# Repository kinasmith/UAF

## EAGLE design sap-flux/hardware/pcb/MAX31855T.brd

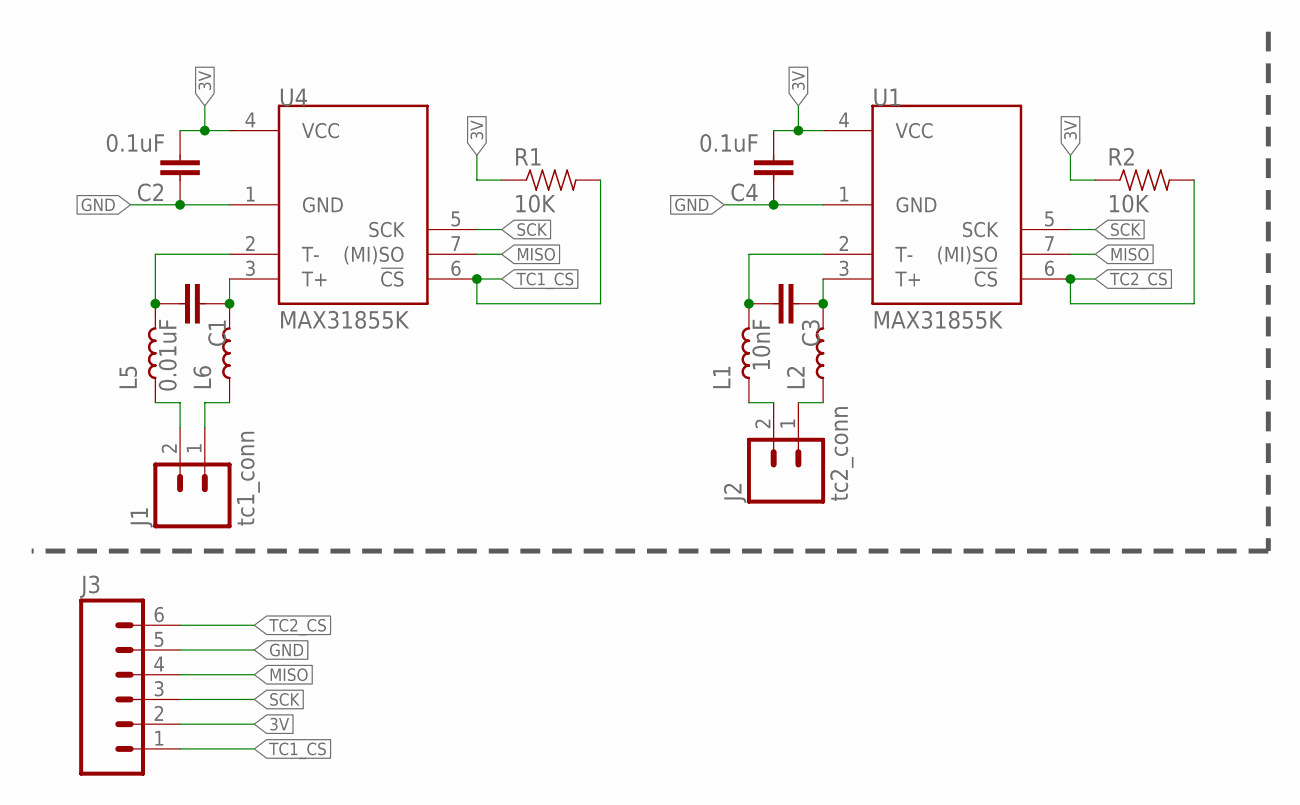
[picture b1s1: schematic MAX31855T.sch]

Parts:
C1: 0.01uF; 0603-CAP
C2, C4: 0.1uF; 0603-CAP
C3: 10nF; 0603-CAP
J1: tc1_conn; 1X02_LONGPADS
J2: tc2_conn; 1X02_LONGPADS
J3: M06LONGPADS; 1X06_LONGPADS
L1, L2, L5, L6: INDUCTOR0603-N; L0603-N
R1, R2: 10K; 0603-RES
U1, U4: MAX31855K; SOIC8

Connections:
3V: C2.2, C4.2, J3.2, R1.1, R2.1, U1.4 (VCC), U4.4 (VCC)
GND: C2.1, C4.1, J3.5, U1.1 (GND), U4.1 (GND)
MISO: J3.4, U1.7 ((MI)SO), U4.7 ((MI)SO)
unnamed: C3.2, L1.2, U1.2 (T-)
unnamed: C3.1, L2.2, U1.3 (T+)
unnamed: J1.1, L6.1
unnamed: J1.2, L5.1
unnamed: J2.1, L2.1
unnamed: C1.2, L5.2, U4.2 (T-)
unnamed: C1.1, L6.2, U4.3 (T+)
unnamed: J2.2, L1.1
SCK: J3.3, U1.5 (SCK), U4.5 (SCK)
TC1_CS: J3.1, R1.2, U4.6 (!CS)
TC2_CS: J3.6, R2.2, U1.6 (!CS)

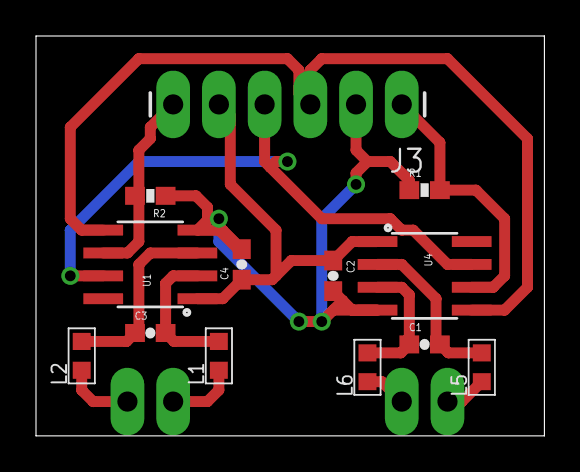
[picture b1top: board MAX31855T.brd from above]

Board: 2 copper layers, 28.2 x 22.2 mm, 15 parts (0 on the bottom side), 14 nets.

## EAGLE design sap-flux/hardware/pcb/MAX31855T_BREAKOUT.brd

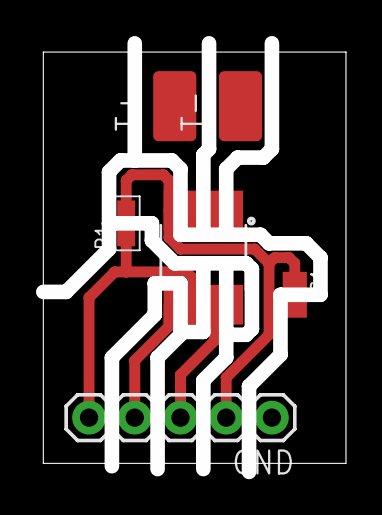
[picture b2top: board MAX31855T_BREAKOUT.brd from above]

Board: 2 copper layers, 16.8 x 22.9 mm, 6 parts (0 on the bottom side), 7 nets.

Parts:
C1: 0.1µF; C0805-L
GND: 1X05
R1: 10k; R0603-N
T+: LUXEON-PAD
T-: LUXEON-PAD
U1: MAX31855K; SOIC8

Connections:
CS: GND.5, R1.1, U1.6
MISO: GND.3, U1.7
unnamed: C1.2, GND.1, U1.1
unnamed: T-.P$1, U1.2
unnamed: T+.P$1, U1.3
unnamed: C1.1, GND.2, R1.2, U1.4
SCK: GND.4, U1.5

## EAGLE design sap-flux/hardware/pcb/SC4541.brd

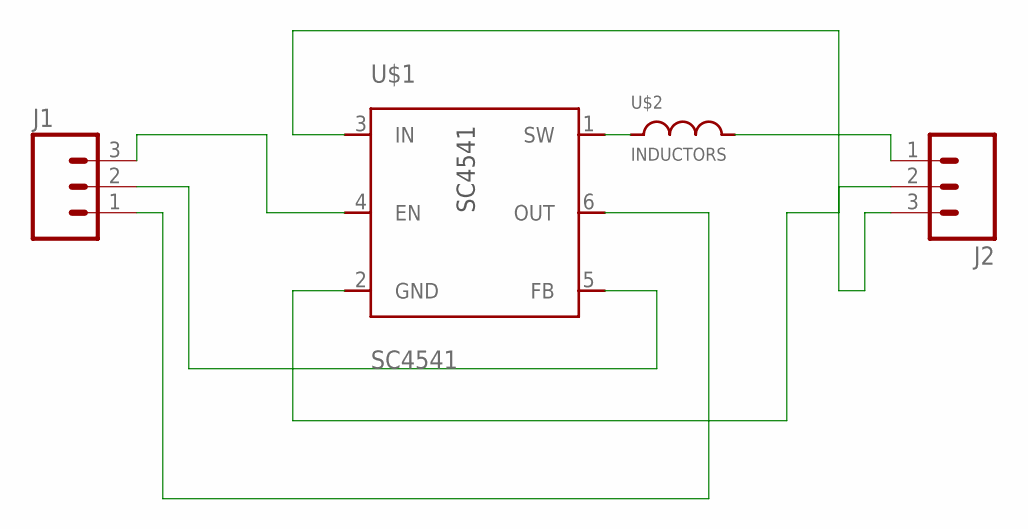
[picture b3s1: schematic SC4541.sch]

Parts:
J1, J2: M03PTH; 1X03
U$1: SC4541; SOT23-6
U$2: INDUCTORS; 1212_3X3

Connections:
unnamed: J1.3, U$1.4 (EN)
unnamed: J1.2, U$1.5 (FB)
unnamed: U$1.1 (SW), U$2.P$2
unnamed: J1.1, U$1.6 (OUT)
unnamed: J2.2, U$1.2 (GND)
unnamed: J2.3, U$1.3 (IN)
unnamed: J2.1, U$2.P$1

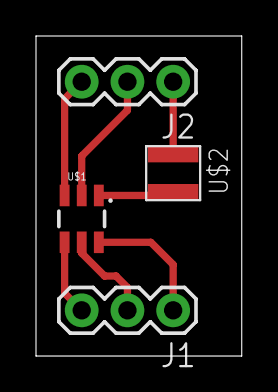
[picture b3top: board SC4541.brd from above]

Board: 2 copper layers, 11.4 x 17.8 mm, 4 parts (0 on the bottom side), 7 nets.

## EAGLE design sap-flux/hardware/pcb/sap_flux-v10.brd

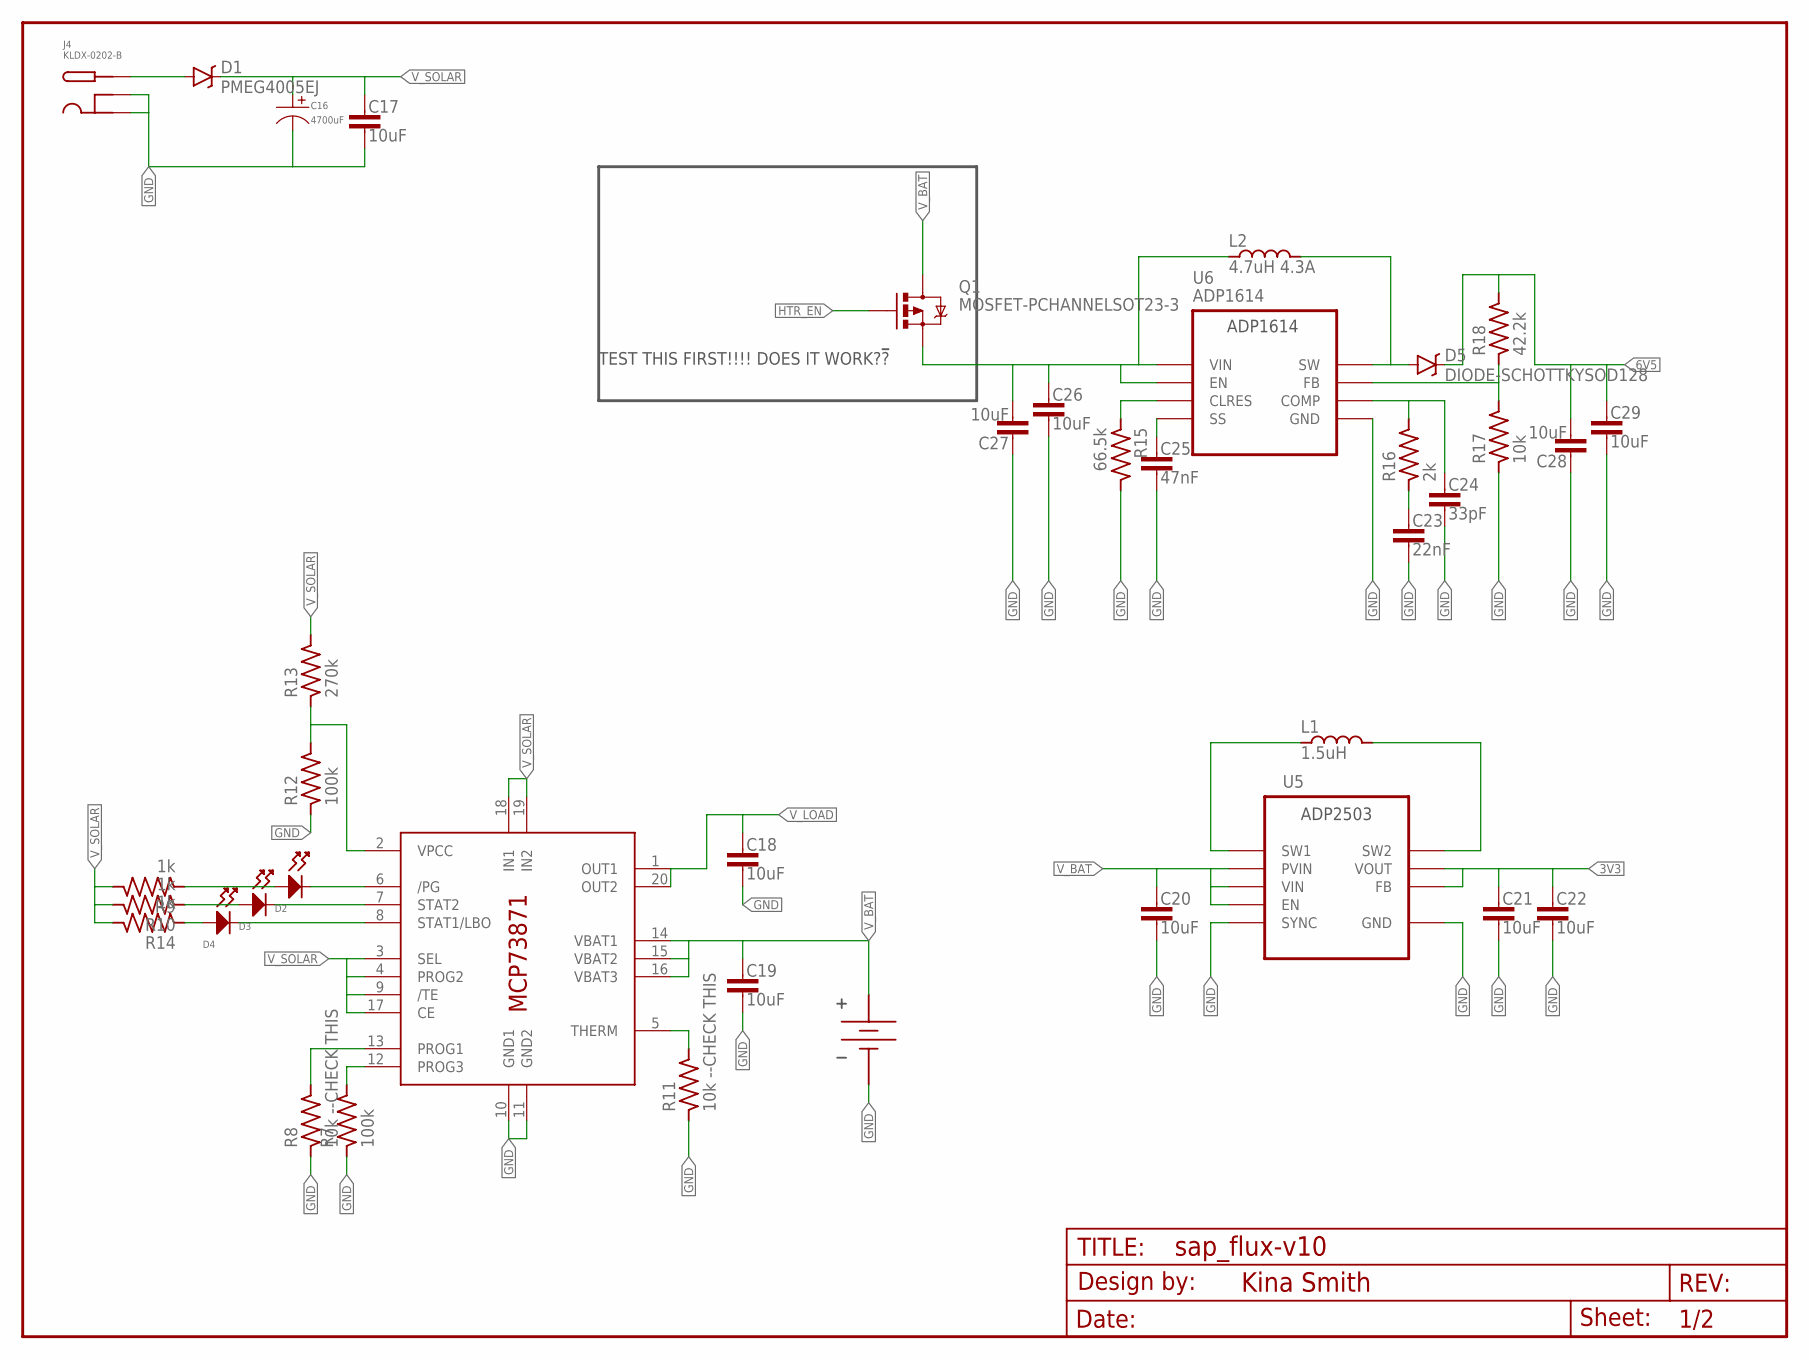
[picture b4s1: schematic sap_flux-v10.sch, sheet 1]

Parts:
BATT1: BATTERY_HOLDER18650; BAT_18650-KEYSTONE-1043
C16: 4700uF; CP10MM
C17, C18, C19, C20, C21, C22, C26, C27, C28, C29: 10uF; C0805-N
C23: 22nF; C0603-N
C24: 33pF; C0603-N
C25: 47nF; C0603-N
D1: PMEG4005EJ; SOD-323
D2, D3, D4: LED_SINGLE-0603; LED0603
D5: DIODE-SCHOTTKYSOD128; SOD128
FRAME1: FRAME-LETTER; CREATIVE_COMMONS
J4: KLDX-0202-B; DC_PWR_JACK; PARTNO FIND THIS PART AND CHECK FOOTPRINT
L1: 1.5uH; L3030
L2: 4.7uH 4.3A; L8080
Q1: MOSFET-PCHANNELSOT23-3; SOT23-3
R7, R12: 100k; R0603-N
R8, R11: 10k --CHECK THIS; R0603-N
R9, R10, R14: 1k; R0603-N
R13: 270k; R0603-N
R15: 66.5k; R0603-N
R16: 2k; R0603-N
R17: 10k; R0603-N
R18: 42.2k; R0603-N
U4: MCP73871; QFN20
U5: ADP2503; DFN300X300X80-11N
U6: ADP1614; DFN300X300X80-11N

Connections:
3V3: C21.1, C22.1, U5.1 (VOUT), U5.10 (FB); also elsewhere on the board
6V5: C28.2, C29.1, D5.C-1 (C), R18.2
6V5_VIN: C26.1, C27.2, L2.1, Q1.2 (S), U6.3 (EN), U6.8 (VIN)
GND: BATT1.NEG (GND), C16.P$2, C17.2, C18.2, C19.2, C20.2, C21.2, C22.2, C23.2, C24.2, C25.2, C26.2, C27.1, C28.1, C29.2, J4.SLEEVE1 (SLEEVE), J4.SLEEVE2 (SLEEVE_SHUNT), R7.1, R8.1, R11.1, R12.1, R15.2, R17.1, U4.10 (GND1), U4.11 (GND2), U5.3 (GND), U5.7 (SYNC), U5.9 (GND), U5.11 (GND), U6.4 (GND), U6.5 (GND), U6.11 (GND); also elsewhere on the board
HTR_EN: Q1.1 (G)
unnamed: D1.A, J4.PIN
unnamed: D2.CATHODE, U4.6 (/PG)
unnamed: R12.2, R13.1, U4.2 (VPCC)
unnamed: D3.CATHODE, U4.7 (STAT2)
unnamed: D4.CATHODE, U4.8 (STAT1/LBO)
unnamed: R8.2, U4.13 (PROG1)
unnamed: R7.2, U4.12 (PROG3)
unnamed: D2.ANODE, R9.1
unnamed: D3.ANODE, R10.1
unnamed: D4.ANODE, R14.1
unnamed: L1.P$1, U5.4 (SW1)
unnamed: L1.P$2, U5.2 (SW2)
unnamed: C25.1, U6.10 (SS)
unnamed: R15.1, U6.9 (CLRES)
unnamed: D5.A-2 (A), L2.2, U6.6 (SW), U6.7 (SW)
unnamed: R17.2, R18.1, U6.2 (FB)
unnamed: C24.1, R16.2, U6.1 (COMP)
unnamed: C23.1, R16.1
V_BAT: BATT1.POS (VBAT), C19.1, C20.1, Q1.3 (D), U4.14 (VBAT1), U4.15 (VBAT2), U4.16 (VBAT3), U5.5 (PVIN), U5.6 (EN), U5.8 (VIN)
V_LOAD: C18.1, U4.1 (OUT1), U4.20 (OUT2)
V_SOLAR: C16.P$1, C17.1, D1.C, R9.2, R10.2, R13.2, R14.2, U4.3 (SEL), U4.4 (PROG2), U4.9 (/TE), U4.17 (CE), U4.18 (IN1), U4.19 (IN2)

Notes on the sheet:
TEST THIS FIRST!!!! DOES IT WORK?!?!

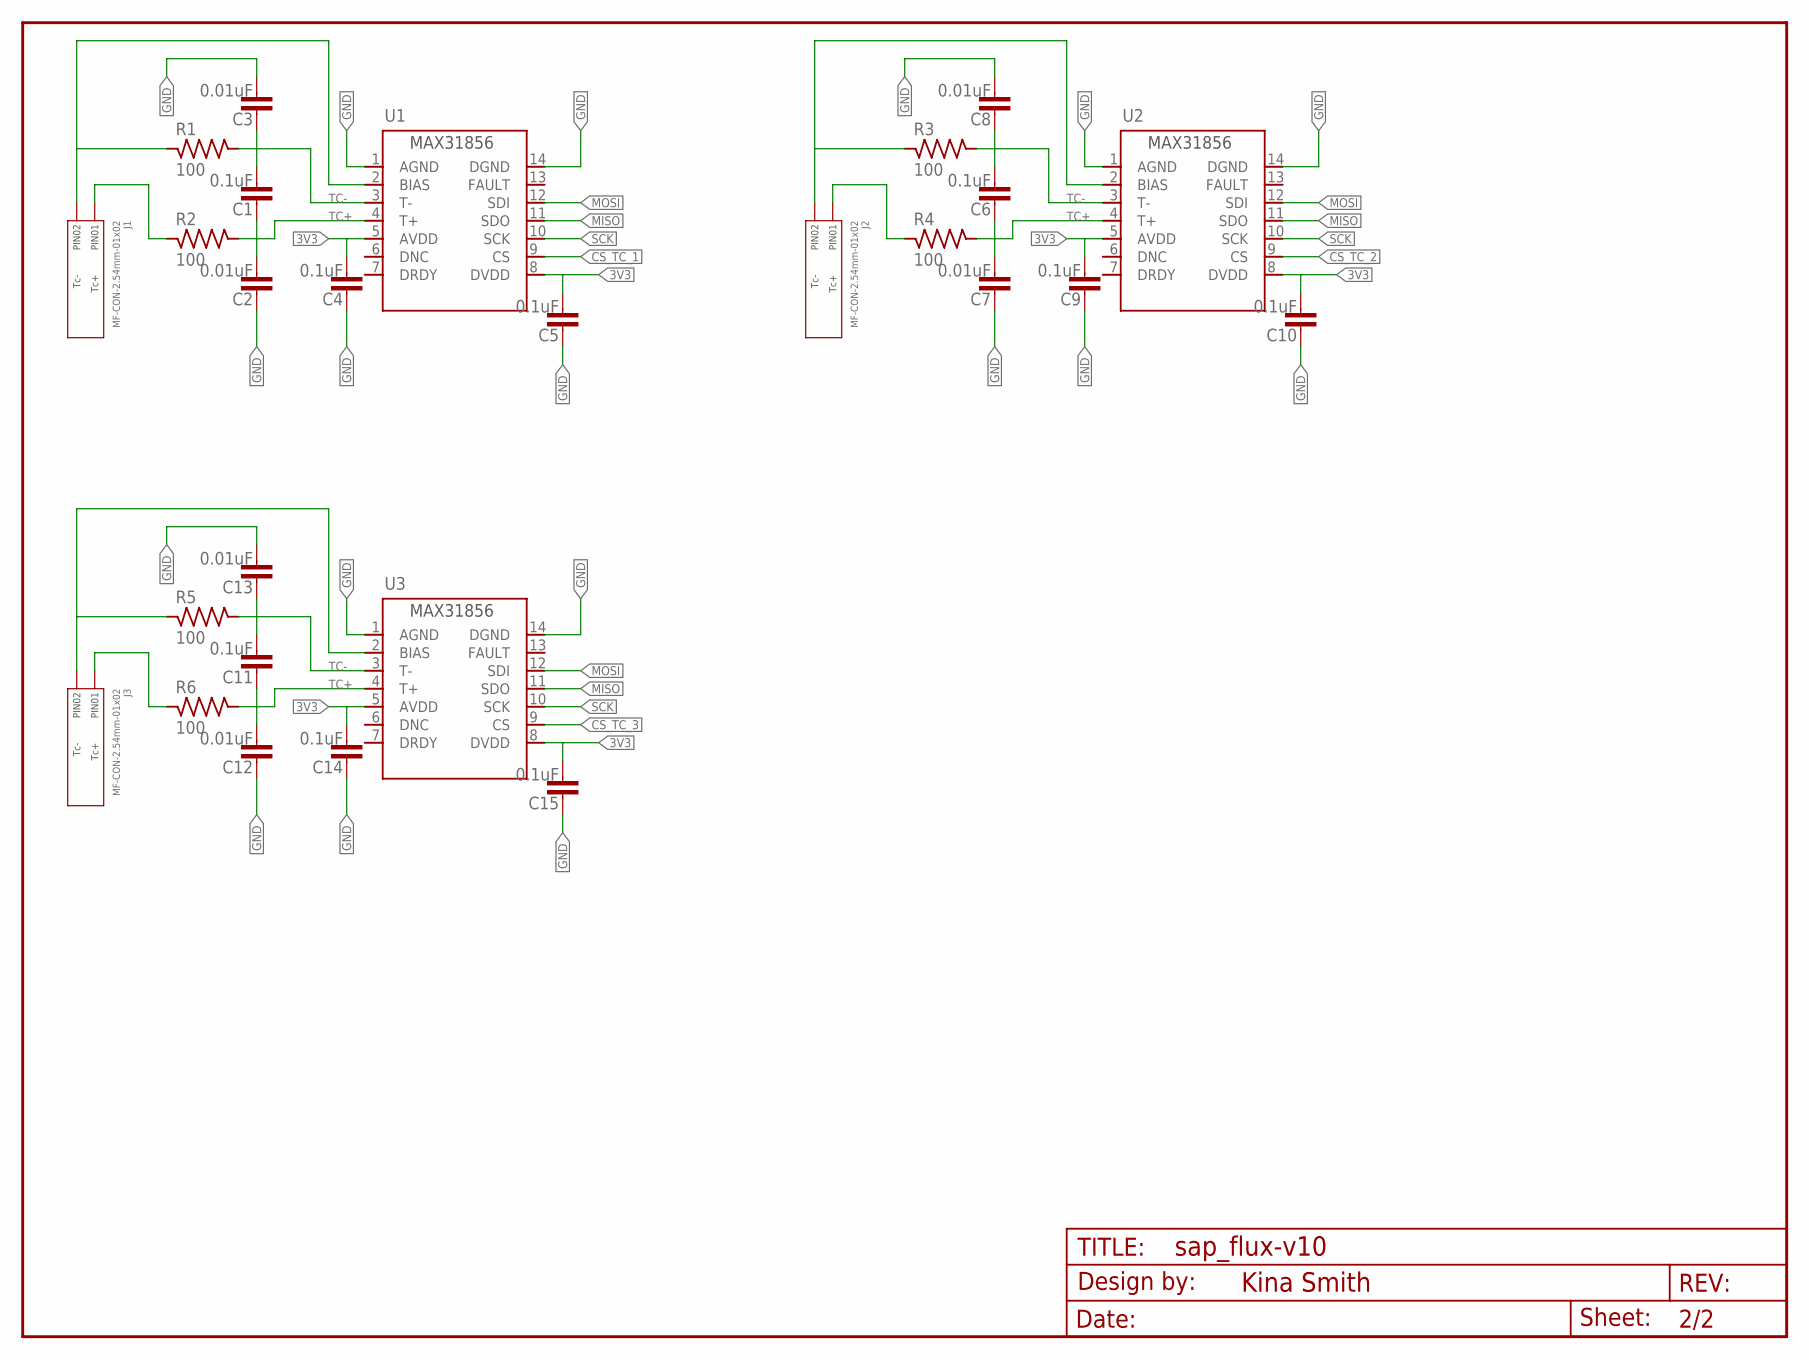
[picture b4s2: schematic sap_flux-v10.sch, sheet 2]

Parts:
C1, C4, C5, C6, C9, C10, C11, C14, C15: 0.1uF; C0603-N
C2, C3, C7, C8, C12, C13: 0.01uF; C0603-N
FRAME2: FRAME-LETTERNO_PACKAGE; DUMMY
J1, J2, J3: MF-CON-2.54mm-01x02; PTH_2.54MM_01X02
R1, R2, R3, R4, R5, R6: 100; R0603-N
U1, U2, U3: MAX31856MUD+; TSSOP14

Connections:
3V3: C4.2, C5.2, C9.2, C10.2, C14.2, C15.2, U1.5 (AVDD), U1.8 (DVDD), U2.5 (AVDD), U2.8 (DVDD), U3.5 (AVDD), U3.8 (DVDD); also elsewhere on the board
CS_TC_1: U1.9 (CS)
CS_TC_2: U2.9 (CS)
CS_TC_3: U3.9 (CS)
GND: C2.1, C3.2, C4.1, C5.1, C7.1, C8.2, C9.1, C10.1, C12.1, C13.2, C14.1, C15.1, U1.1 (AGND), U1.14 (DGND), U2.1 (AGND), U2.14 (DGND), U3.1 (AGND), U3.14 (DGND); also elsewhere on the board
MISO: U1.11 (SDO), U2.11 (SDO), U3.11 (SDO)
MOSI: U1.12 (SDI), U2.12 (SDI), U3.12 (SDI)
unnamed: J2.P$1 (PIN1), R4.1
unnamed: J2.P$2 (PIN2), R3.1, U2.2 (BIAS)
unnamed: J3.P$1 (PIN1), R6.1
unnamed: J3.P$2 (PIN2), R5.1, U3.2 (BIAS)
unnamed: J1.P$1 (PIN1), R2.1
unnamed: J1.P$2 (PIN2), R1.1, U1.2 (BIAS)
SCK: U1.10 (SCK), U2.10 (SCK), U3.10 (SCK)
TC+: C1.1, C2.2, C6.1, C7.2, C11.1, C12.2, R2.2, R4.2, R6.2, U1.4 (T+), U2.4 (T+), U3.4 (T+)
TC-: C1.2, C3.1, C6.2, C8.1, C11.2, C13.1, R1.2, R3.2, R5.2, U1.3 (T-), U2.3 (T-), U3.3 (T-)

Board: 2 copper layers, 68 parts (0 on the bottom side), 36 nets, no tracks yet.

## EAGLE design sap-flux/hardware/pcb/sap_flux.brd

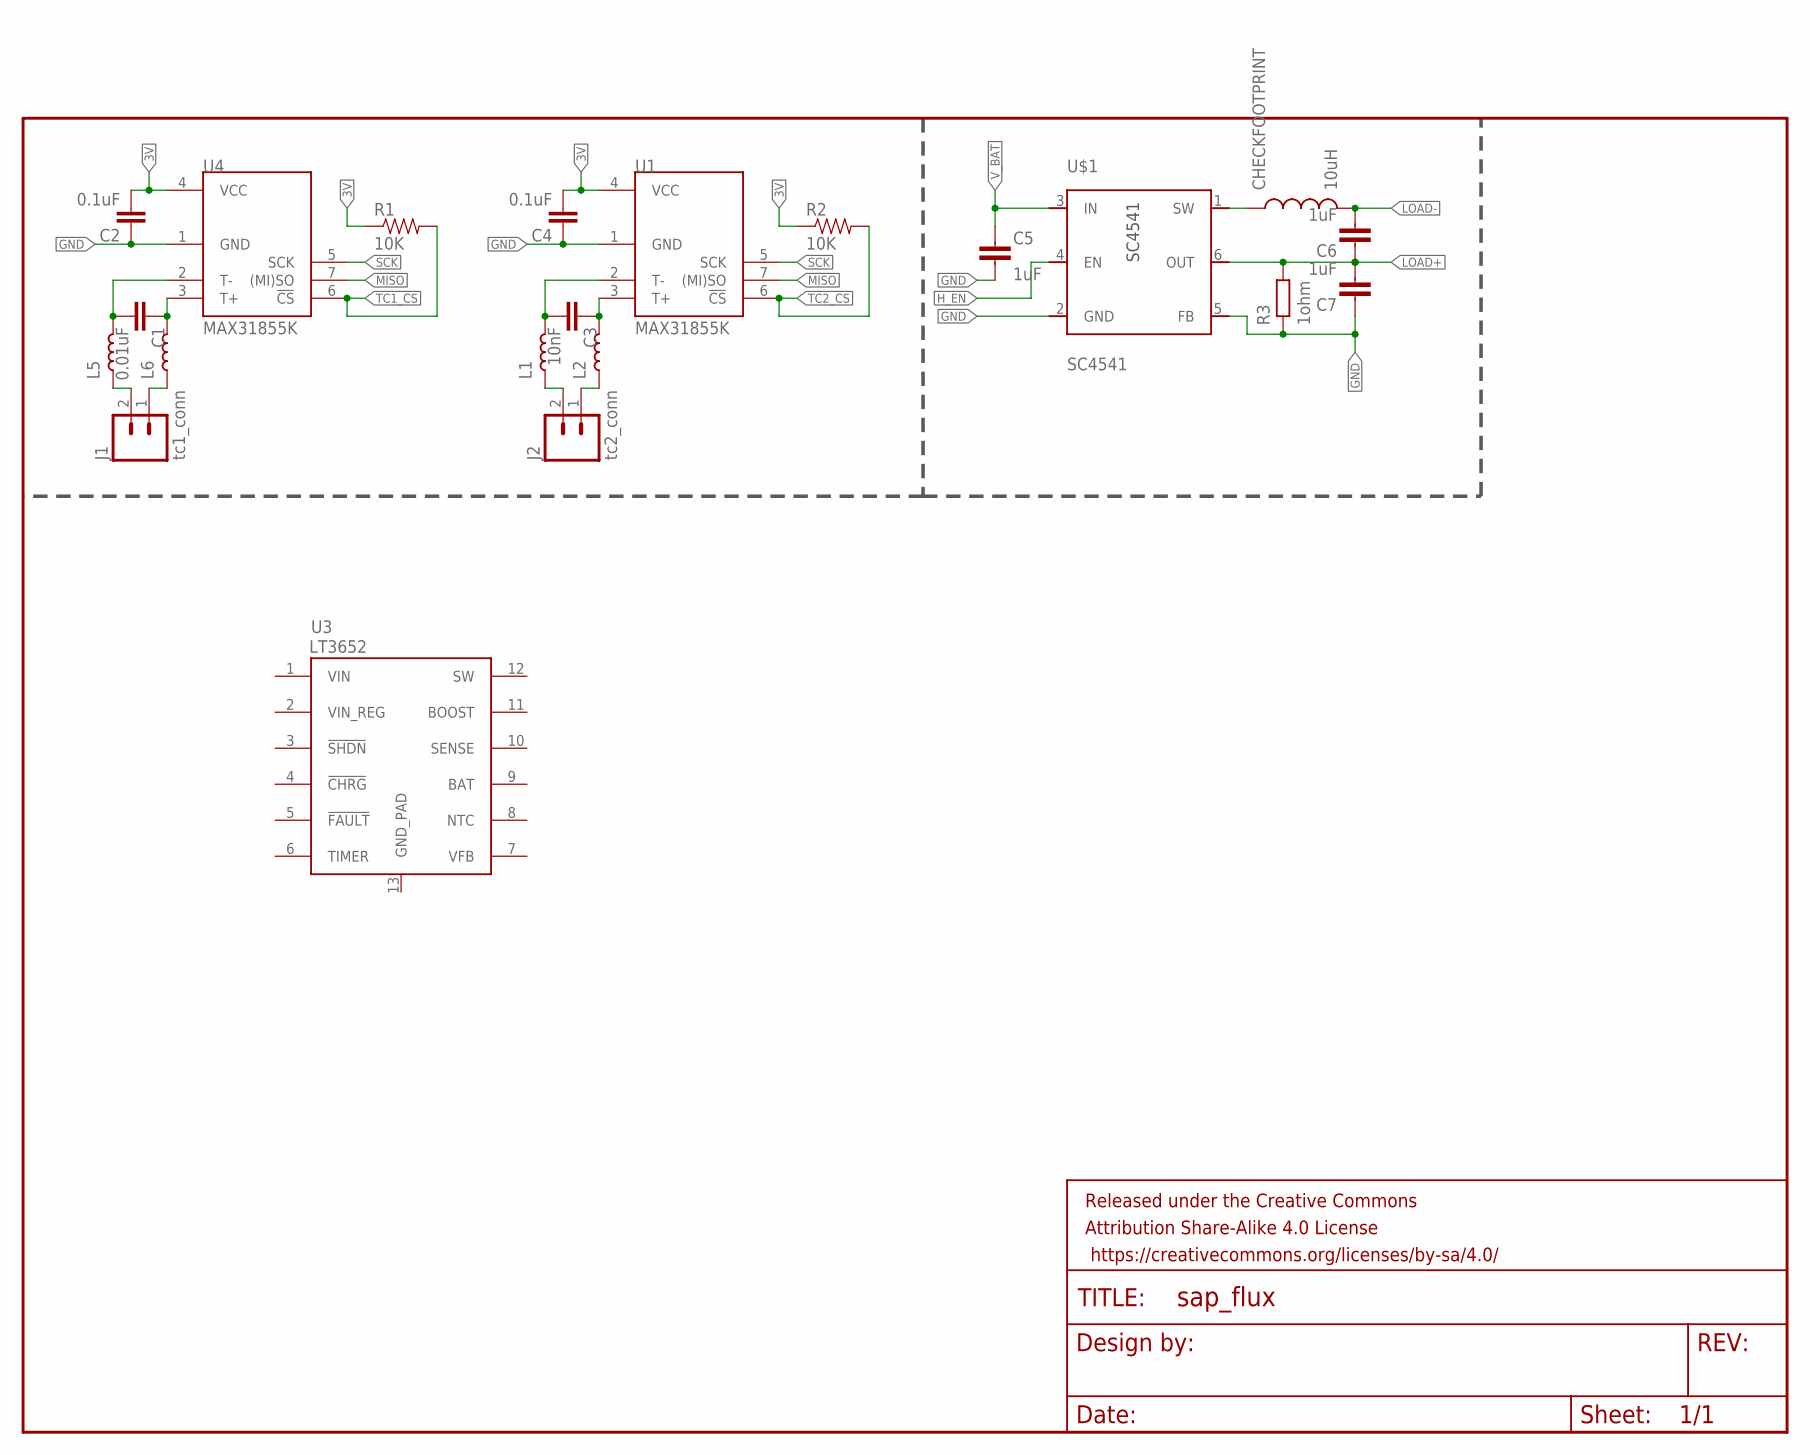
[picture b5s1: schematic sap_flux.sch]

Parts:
C1: 0.01uF; 0603-CAP
C2, C4: 0.1uF; 0603-CAP
C3: 10nF; 0603-CAP
C5, C6, C7: 1uF; C0603-N
CHECKFOOTPRINT: 10uH; INDUCTOR_SDR1307
FRAME2: FRAME-LETTER; CREATIVE_COMMONS
J1: tc1_conn; 1X02_LONGPADS
J2: tc2_conn; 1X02_LONGPADS
L1, L2, L5, L6: INDUCTOR0603-N; L0603-N
R1, R2: 10K; 0603-RES
R3: 1ohm; R0603-N
U1, U4: MAX31855K; SOIC8
U3: LT3652; MSOP-12_GND
U$1: SC4541; SOT23-6

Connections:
3V: C2.2, C4.2, R1.1, R2.1, U1.4 (VCC), U4.4 (VCC)
GND: C2.1, C4.1, C5.2, C7.1, R3.1, U1.1 (GND), U4.1 (GND), U$1.2 (GND), U$1.5 (FB)
H_EN: U$1.4 (EN)
LOAD+: C6.1, C7.2, R3.2, U$1.6 (OUT)
LOAD-: C6.2, CHECKFOOTPRINT.P$2 (2)
MISO: U1.7 ((MI)SO), U4.7 ((MI)SO)
unnamed: C3.2, L1.2, U1.2 (T-)
unnamed: C3.1, L2.2, U1.3 (T+)
unnamed: C1.2, L5.2, U4.2 (T-)
unnamed: C1.1, L6.2, U4.3 (T+)
unnamed: CHECKFOOTPRINT.P$1 (1), U$1.1 (SW)
SCK: U1.5 (SCK), U4.5 (SCK)
TC1_CS: R1.2, U4.6 (!CS)
TC2_CS: R2.2, U1.6 (!CS)
V_BAT: C5.1, U$1.3 (IN)

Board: 2 copper layers, 22 parts (0 on the bottom side), 14 nets, no tracks yet.

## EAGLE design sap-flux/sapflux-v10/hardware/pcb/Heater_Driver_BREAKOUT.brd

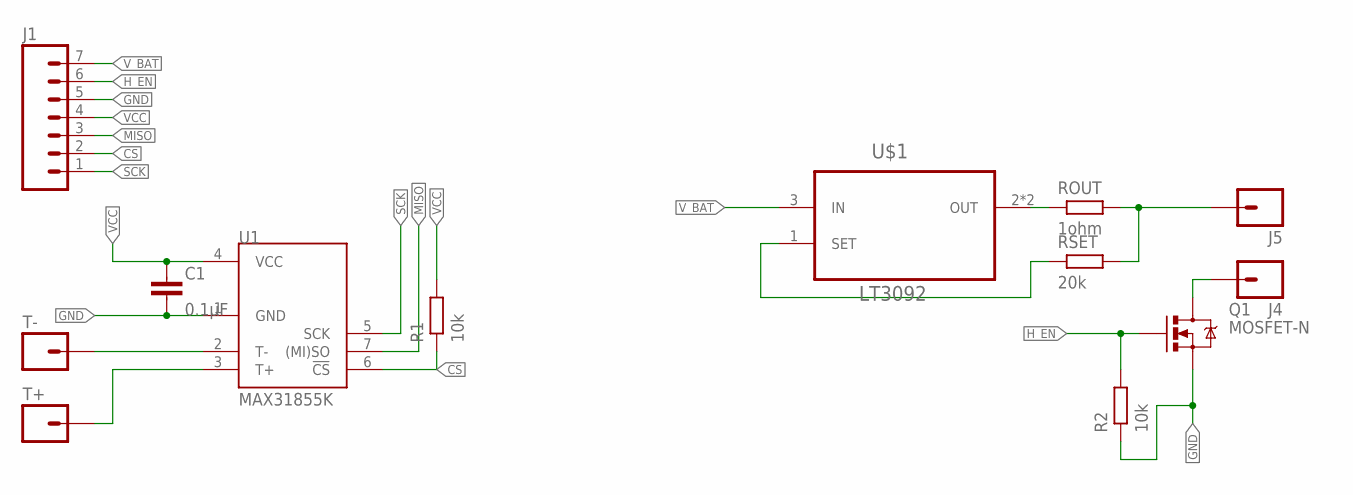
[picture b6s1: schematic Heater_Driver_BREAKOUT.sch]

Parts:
C1: 0.1µF; C0603-N
J1: M07; 1X07
J4, J5: M01SMD; LUXEON-PAD
Q1: MOSFET-N; SOT23-3
R1, R2: 10k; R0603-N
ROUT: 1ohm; R0603-N
RSET: 20k; R0603-N
T+: M01SMD; LUXEON-PAD
T-: M01SMD; LUXEON-PAD
U1: MAX31855K; SOIC8
U$1: LT3092; SOT223

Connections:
CS: J1.2, R1.1, U1.6 (!CS)
GND: C1.2, J1.5, Q1.2 (S), R2.1, U1.1 (GND)
H_EN: J1.6, Q1.1 (G), R2.2
MISO: J1.3, U1.7 ((MI)SO)
unnamed: T-.P$1, U1.2 (T-)
unnamed: T+.P$1, U1.3 (T+)
unnamed: RSET.1, U$1.1 (SET)
unnamed: ROUT.1, U$1.2 (OUT), U$1.4 (OUT)
unnamed: J5.P$1, ROUT.2, RSET.2
unnamed: J4.P$1, Q1.3 (D)
SCK: J1.1, U1.5 (SCK)
VCC: C1.1, J1.4, R1.2, U1.4 (VCC)
V_BAT: J1.7, U$1.3 (IN)

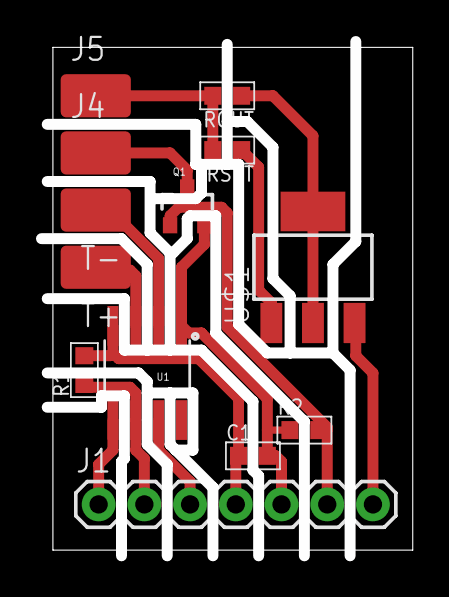
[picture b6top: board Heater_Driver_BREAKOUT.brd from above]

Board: 2 copper layers, 20.6 x 28.6 mm, 13 parts (0 on the bottom side), 13 nets.

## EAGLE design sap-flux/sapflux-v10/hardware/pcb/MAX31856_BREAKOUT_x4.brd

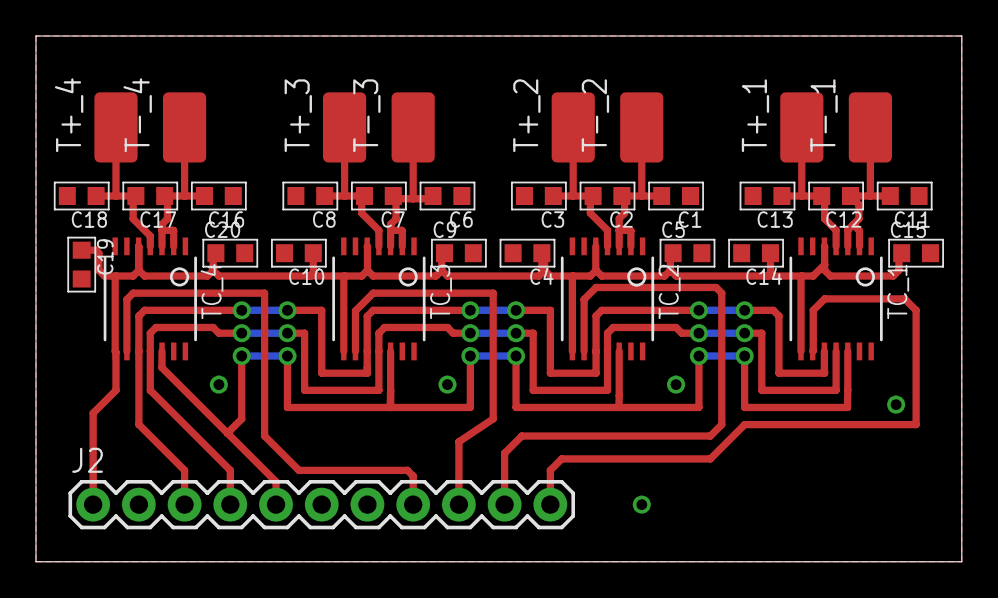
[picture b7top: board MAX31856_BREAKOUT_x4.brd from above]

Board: 2 copper layers, 51.4 x 29.2 mm, 33 parts (0 on the bottom side), 17 nets.

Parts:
C1, C3, C6, C8, C11, C13, C16, C18: 0.01µF; C0603-N
C2, C4, C5, C7, C9, C10, C12, C14, C15, C17, C19, C20: 0.1µF; C0603-N
J2: 1X11
T+_1, T+_2, T+_3, T+_4: LUXEON-PAD
T-_1, T-_2, T-_3, T-_4: LUXEON-PAD
TC_1, TC_2, TC_3, TC_4: MAX31856MUD+; TSSOP14

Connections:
3V3: C4.1, C5.1, C9.1, C10.1, C14.1, C15.1, C19.1, C20.1, J2.1, TC_1.5, TC_1.8, TC_2.5, TC_2.8, TC_3.5, TC_3.8, TC_4.5, TC_4.8
CS_1: J2.11, TC_1.9
CS_2: J2.10, TC_2.9
CS_3: J2.9, TC_3.9
CS_4: J2.8, TC_4.9
GND: C1.1, C3.2, C4.2, C5.2, C6.1, C8.2, C9.2, C10.2, C11.1, C13.2, C14.2, C15.2, C16.1, C18.2, C19.2, C20.2, J2.2, TC_1.1, TC_1.14, TC_2.1, TC_2.14, TC_3.1, TC_3.14, TC_4.1, TC_4.14
MISO: J2.4, TC_1.11, TC_2.11, TC_3.11, TC_4.11
MOSI: J2.5, TC_1.12, TC_2.12, TC_3.12, TC_4.12
unnamed: C7.2, C8.1, T+_3.P$1, TC_3.4
unnamed: C6.2, C7.1, T-_3.P$1, TC_3.2, TC_3.3
unnamed: C2.2, C3.1, T+_2.P$1, TC_2.4
unnamed: C1.2, C2.1, T-_2.P$1, TC_2.2, TC_2.3
unnamed: C12.2, C13.1, T+_1.P$1, TC_1.4
unnamed: C11.2, C12.1, T-_1.P$1, TC_1.2, TC_1.3
unnamed: C17.2, C18.1, T+_4.P$1, TC_4.4
unnamed: C16.2, C17.1, T-_4.P$1, TC_4.2, TC_4.3
SCK: J2.3, TC_1.10, TC_2.10, TC_3.10, TC_4.10

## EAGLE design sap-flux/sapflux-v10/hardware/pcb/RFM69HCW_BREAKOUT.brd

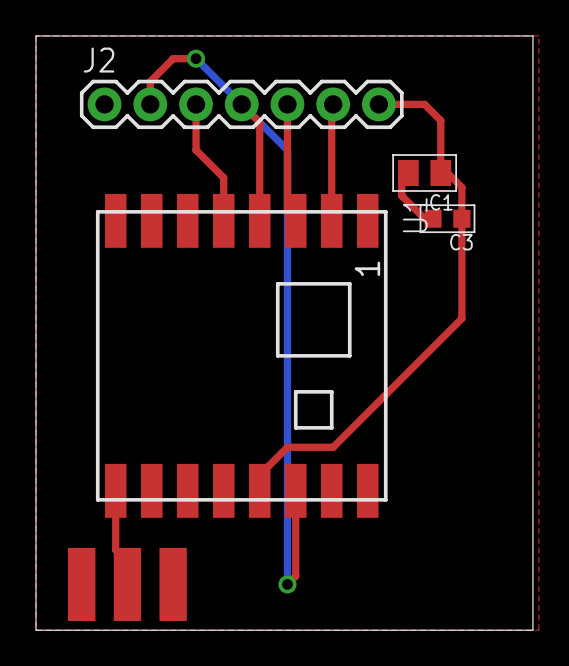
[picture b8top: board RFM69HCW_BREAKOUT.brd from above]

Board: 2 copper layers, 27.6 x 33.0 mm, 5 parts (0 on the bottom side), 8 nets.

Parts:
C1: 10µF; C0805-N
C3: 0.1µF; C0603-N
J2: 1X07
J$1: SMA_EDGE; SMA-EDGE
U1: RFM69HCW; RFM69HCW-XXXS2

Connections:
ANT: J$1.SIG, U1.9
GND: C1.2, C3.2, J2.1, J$1.GND@0, J$1.GND@1, J$1.GND@2, J$1.GND@3, U1.1, U1.8, U1.10
INT: J2.2, U1.14
MISO: J2.6, U1.2
MOSI: J2.5, U1.3
NSS: J2.3, U1.5
SCK: J2.4, U1.4
VCC: C1.1, C3.1, J2.7, U1.13

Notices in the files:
parts and their libraries:
SparkFun-AnalogIC: Licensing:Creative Commons ShareAlike 4.0 International - https://creativecommons.org/licenses/by-sa/4.0
My_Aesthetics: Released under the Creative Commons Attribution Share-Alike 4.0 License
My_Aesthetics: https://creativecommons.org/licenses/by-sa/4.0
